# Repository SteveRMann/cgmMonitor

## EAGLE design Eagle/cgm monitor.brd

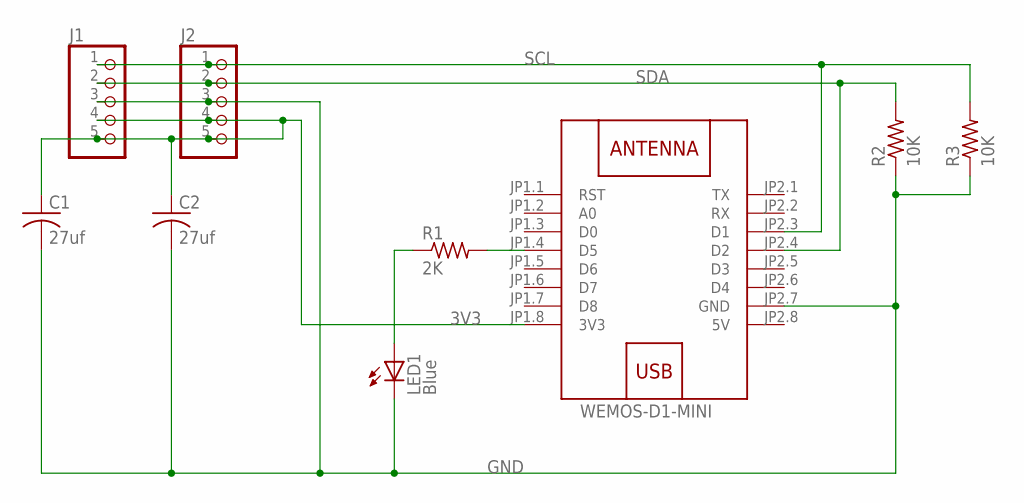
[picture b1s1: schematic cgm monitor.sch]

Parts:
C1, C2: 27uf; C050-050X075
J1, J2: PINHD-1X5; 1X05
LED1: Blue; LED5MM
R1: 2K; 0207/9
R2, R3: 10K; 0207/9
W1: WEMOS-D1-MINI

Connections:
3V3: C1.1, C2.1, J1.4, J1.5, J2.4, J2.5, W1.JP1.8 (3V3)
5V: W1.JP2.8 (5V)
GND: C1.2, C2.2, J1.3, J2.3, LED1.K (C), R2.1, R3.1, W1.JP2.7 (GND)
unnamed: R1.2, W1.JP1.4 (D5)
unnamed: LED1.A, R1.1
SCL: J1.1, J2.1, R3.2, W1.JP2.3 (D1)
SDA: J1.2, J2.2, R2.2, W1.JP2.4 (D2)

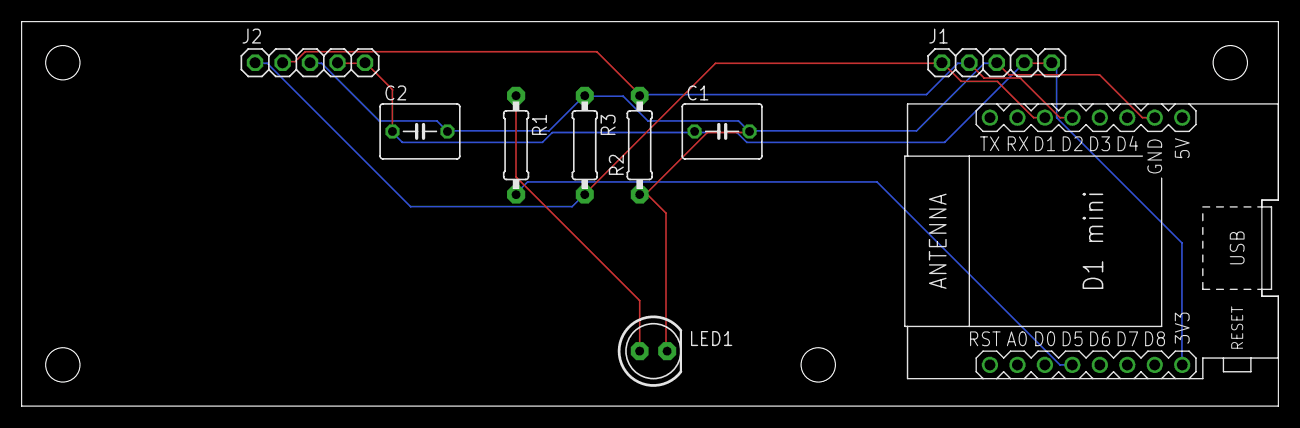
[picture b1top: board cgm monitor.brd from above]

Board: 2 copper layers, 116.2 x 35.5 mm, 9 parts (0 on the bottom side), 6 nets.

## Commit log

2021-11-11 Added rssiTopic
2021-11-11 Bump the version number
2021-11-11 Added showRssi()
2021-11-11 Removed alarm, moved functions, blink on WiFi
    Removed alarm,
    moved functions to functions tab,
    Make LED blink during WiFi connect.
2021-11-11 Update OTA
2021-11-11 Deleted connectName, renamed setup_wifi tab
2021-11-11 Renamed reconnect to mqtt
2022-03-02 Added SSID printout
2022-03-02 Changed WiFi to WFiMulti
2022-03-20 Added gitignore, Cleaned up SSID display, simplified the unique name selection
2022-04-05 Removed errant comment
2022-09-12 Recompiled for Workshop unit
2022-12-21 Test setup_wifiMulti
    Added a test to setup_wifiMulti to return an error if WiFi connection fails.
2022-12-25 Stale timer stuff
    Reimagined how the stale ticker is used. Staleticker gets reset when any MQTT message arrived. If no message is received in two minutes, the ESP is rebooted.
2022-12-26 Added test for WiFi in loop
2023-05-21 Added a USB notch and flipped D1 to my standard orientation
2023-05-22 Added the USB notch to the PCB
2023-11-08 Removed WiFiMulti
    Removed WiFiMulti
2023-11-27 Updated ssid list, increased PubSub timeout
    Added a test device, updates the SSID list.
    Increased the PubSub timeout
2024-01-17 Changed crashTimer to unsigned long
    Was an int.
2024-02-11 Cleaned up, V5.01
    Cleaned up, V5.01
2024-02-20 Update cgm.ino
    Added
    #define MacABA962 //Latest build
2025-12-05 PCB updates
2025-12-05 Version 5.02
    Reverted back to MQTT at 192.168.1.124
2025-12-05 Added test Wemos
2025-12-05 Added test Wemos MAC
    Update MAC addresses
2025-12-05 Update cgm.ino
    MAC changes
2025-12-14 Version 5.02
    Started adding battery charge indicator
2025-12-16 Using HA_MQTT server
2025-12-17 Cleaned up comments
2025-12-18 Version 5.04
    Back to MQTT broker on 192.168.1.57
2025-12-18 Version 5.05
    Reduced the MAC definitions in cgm.ino
2025-12-24 Made the LED to be a battery indicator
2025-12-24 Adjusted timing
2025-12-24 Fine tune the blink timing
2025-12-25 Changed Battery LED to PWM
2025-12-25 Added D5 and D6
    Some of the PCBs have the LED on D5 and some on D6.
2026-01-02 Create LDR-test.ino
    Test the LDR on A0

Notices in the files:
parts and their libraries:
diy-modules: Released under the Creative Commons Attribution 4.0 International License: http://creativecommons.org/licenses/by/4.0
